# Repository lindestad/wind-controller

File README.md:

# LINDESTAD wind controller

Reproducible ESP32-C3 / Zephyr firmware and KiCad PCB for a four-fan simracing wind simulator.

[Hardware and manufacturing files](hardware/README.md) · [Schematic](hardware/reports/schematic.pdf) · [BOM](hardware/BOM.csv) · [Host integration](docs/host-integration.md)

The images are CAD renderings; representative USB/jack/eFuse models are visual aids.

Zephyr application for WindPCB B.3, ESP32-C3-WROOM-02-N4, four ARCTIC P14 Pro PST fans. Uses native USB Serial/JTAG, four 25 kHz hardware PWM outputs and four tach inputs. No external programmer is required for blank-flash recovery.

The assembled B.3 board is working. On 22 September 2026 it was programmed over native USB, tested with one and then two fans, and integrated with SimHub through Rig Companion. Live full-demand readings were approximately 2,470 and 2,410 RPM (fan rating 2,500 RPM); the user confirmed good airflow after correcting a reversed fan. This is functional bring-up evidence, not calibrated electrical or thermal qualification. See [validation scope](docs/validation.md).

## Repository layout

- `src/`, `include/`, `boards/`: firmware and custom Zephyr board definition.
- `hardware/`: native KiCad project, local libraries/models, BOM, Gerbers, CPL, STEP, PDFs, renders and exporter.
- `scripts/`, `tests/`: dependency setup, build, pin audit, stop-first flash and executable host tests.
- `integrations/simhub/`: source snapshot of the companion's SimHub bridge; no proprietary SDK DLLs.
- `reports/`: historical software/build/bring-up evidence, not a substitute for rerunning checks.

## Build

Windows workspace: `../wind-zephyr`, pinned to Zephyr **v4.4.2**. The required complete Zephyr SDK **1.0.1** is installed under `~/zephyr-sdk-1.0.1`. This project is a separate Git repository; SDK and dependency repositories are outside it.

Install Git, Python 3.12 (including `py`), CMake, Ninja and a host GCC (for the tests; Strawberry Perl's GCC works on Windows). Install the complete **Zephyr SDK 1.0.1** at `~/zephyr-sdk-1.0.1`, or pass its directory with `-Sdk`. Fetch the pinned source dependencies once:

```powershell
./scripts/setup.ps1
./scripts/build.ps1 -Pristine
../wind-zephyr/.venv/Scripts/python.exe tests/test_control.py
```

`build/zephyr/zephyr.bin` is the application build output. Use the Zephyr runner's generated flash configuration rather than guessing offsets. Build provenance and configuration checks are recorded in `reports/`. See `docs/validation.md` for scope and hardware acceptance items.

To recreate dependencies, create a Python 3.12 virtual environment in `../wind-zephyr/.venv`, install `west`, initialize the official Zephyr manifest at v4.4.2, run `west update`, install `zephyr/scripts/requirements.txt`, and run `west blobs fetch hal_espressif`. Use SDK 1.0.1. The frozen manifest is stored in `reports/west-frozen.yml`. No global Zephyr workspace was changed.

## USB and SimHub

Hold BOOT, press/release RESET, release BOOT. The ROM downloader should enumerate through USB-C even if application flash is blank. Connect a data-capable cable; barrel power is unnecessary for flashing. Run `west flash --esp-device COMx` from this workspace with the build directory specified, then press RESET if needed. The exact runner command is documented by `west flash -H -r esp32` and must match the installed esptool version. No eFuse/security programming or UART bridge is required.

For direct integration without Rig Companion, use SimHub **Custom Serial Devices**, sending ASCII `W,<left>,<right>\n` with integer demands 0–1000. The final character is one LF byte. Send every 100 ms or faster, including unchanged values. There is no Arduino/ShakeIt protocol emulation. USB returns the structured status frames below; Zephyr console/log noise remains disabled. Displaying warnings in SimHub needs a receiver/integration; transmission alone does not create a SimHub warning UI.

Zero and demands below 50 stop that side. A nonzero request first precharges for 750 ms, then attempts the commanded headers individually. Each gets a 250 ms full-speed kick; the next starts after at least 500 ms and three new filtered tach edges, or after a 2 s timeout if tach is absent. That timeout raises a per-header warning and advances the sequence, without stopping any output. Losing tach for 2 s after startup also warns while maintaining the requested duty. One to four fans may occupy any headers; no fan-count setting is required. Even zero fans produces warnings rather than a shutdown. Missing headers can delay later fans by 2 s each (up to 6.75 s from command to the fourth header's kick).

An empty header, stalled motor and broken tach wire cannot be distinguished electrically. Warnings mean **no tach while commanded**, not a confirmed missing fan. There are no repeated automatic startup kicks. Three new edges clear a warning; stopping that side clears its warning and the next start checks again. Do not hot-plug fans; switch off supplies before moving connectors.

Every 500 ms, USB transmits `S,1,<mode>,<mask>\n` (8 ASCII bytes). Version is 1; mode is `0` off, `1` precharging, `2` active (including warnings), `3` command timeout, or `4` fault. Mask is one uppercase hexadecimal digit: bits `1/2/4/8` correspond to L1/L2/R1/R2 without tach. For example `S,1,2,A\n` means active, with L2 and R2 warnings. Warnings are live and only apply after a startup attempt, so a clear mask at boot does not prove a fan is connected. STATUS stays lit when fan power is enabled. The red FAULT LED remains controlled by the hardware eFuse, not these firmware warnings.

Status transmission uses a bounded interrupt-driven buffer; a host that stops reading cannot block the control loop or command timeout. Pending reports can be stale after a host pause; a receiver must wait for fresh periodic reports before relying on them. Reports describe requested controller state, not measured fan-supply voltage or verified motor motion.

Only valid complete demand frames refresh the 500 ms command deadline. Overlong, malformed and partial frames are rejected. RX-budget saturation and output failures still stop operation and require reset; warnings do not bypass these protections. Commanded stop sets all PWM inputs low before removing fan power. Abrupt USB loss/reset can still cause the documented brief capacitor-powered twitch/coasting.

## Extended telemetry

Extended telemetry is also sent about once per second: `T,2,<mode>,<warning_hex>,<uptime_ms>,<accepted>,<rejected>,<rpm_L1>,<rpm_L2>,<rpm_R1>,<rpm_R2>,<pwm_L1>,<pwm_L2>,<pwm_R1>,<pwm_R2>\n`. RPM uses edge-count differences over the actual sample interval and assumes two pulses per revolution; absolute accuracy needs independent measurement. PWM values are per-header 0–1000 output demands including startup kicks. No supply voltage/current/temperature measurement exists. The existing S1 reports remain unchanged; consumers should ignore recognized additional report types. Rig Companion now owns USB and receives SimHub vehicle speed through its localhost bridge; see [host integration](docs/host-integration.md).

## Routine firmware updates

After building, use Rig Companion’s **Release USB for firmware update** button (or close any direct serial owner) and run `./scripts/flash.ps1 -Port COM4` (substitute the current port). The helper sends stop commands, requires repeated OFF reports for two seconds, then invokes the generated Zephyr flash runner. It aborts if it cannot confirm OFF. Firmware starts with fan power disabled and needs a new valid demand before running. Never resume the command sender during flashing.

The board's external enable pull-down is intended to keep incoming fan power off in ROM download/reset. This makes leaving 12 V connected a supported design intent for routine updates with the stop-first helper, **not a measured guarantee of no movement**: the MCU cannot measure output capacitor voltage, and reset can release PWM before stored energy drains. Disconnect 12 V whenever zero fan movement matters, or for blank/corrupt firmware recovery. The helper cannot work on older firmware without status reports. Hold BOOT/RESET and use the ordinary Zephyr runner with 12 V disconnected in that case.

The watchdog requests a whole-system reset. The ESP32 driver uses an interrupt stage followed by a reset stage; a configured 500 ms stage interval is approximately 1 s to hardware reset, not a 500 ms reset guarantee. The ordinary command timeout runs separately. No hardware runtime timing guarantee is claimed before measurement.

## Pin map

| Function | GPIO |
|---|---|
| L1/L2/R1/R2 PWM sink gates | 4 / 5 / 6 / 7 |
| L1/L2/R1/R2 tach | 0 / 1 / 3 / 20 |
| Fan power enable | 10 |
| Status LED | 21 |
| Native USB D− / D+ | 18 / 19 |
| BOOT | 9 |
| Reserved boot straps | 2 / 8 |

The DTS uses the WROOM N4 module definition, not a development board with UART0 on GPIO20/21. UART0/1, radios, logging and power management are disabled. The eFuse FLT signal is not wired to the MCU, so firmware cannot classify its faults or measure supply voltage/current.

The LEDC child `inverted` property initializes the stopped output high. Runtime requests use normal polarity and `(1000 − fan_demand) × 40 ns` gate pulse width; the transistor provides the physical inversion. The pinned driver's implementation was checked to distinguish initial idle level from runtime polarity flags.

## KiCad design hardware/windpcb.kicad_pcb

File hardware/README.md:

# WindPCB B.3 — editable hardware and manufacturing release

70 × 64 mm, black solder mask, white silkscreen, two-layer 1.6 mm FR-4 / 1 oz copper.
ESP32-C3-WROOM-02-N4; four ARCTIC P14 Pro PST headers; native USB-C; protected 12 V input.

These are CAD renders, not photographs. J1, J2 and U4 have representative visual bodies;
their manufacturer drawings and electrical pads govern assembly.

## Reproduce the board

1. Install **KiCad 10.0**, including its standard symbol, footprint and 3D libraries.
2. Open `windpcb.kicad_pro`. All project-specific symbols, footprints and visual models
   are under `libraries/`; library tables use `${KIPRJMOD}`. Standard STEP models use
   `${KICAD10_3DMODEL_DIR}`. No files from the author's KiCad folder are needed.
3. Use [BOM.csv](BOM.csv), [schematic PDF](reports/schematic.pdf) and
   [assembly drawing](reports/assembly-top.pdf) to inspect the release.
4. Fabrication input: [Gerber ZIP](manufacturing/windpcb-revb-gerbers.zip), including
   copper, masks, silkscreens, outline, separate PTH/NPTH drilling and front paste.
5. Full assembly inputs: [PCBA BOM](manufacturing/assembly/PCBA-BOM.csv) and
   [PCBA CPL](manufacturing/assembly/PCBA-CPL.csv): **70 placements, 33 MPNs,
   63 SMT + 7 through-hole**. Do not use the SMT-only files for full assembly.
6. Select black mask / white silk, lead-free HASL, top-side assembly, and customer-added
   tooling holes. Retain individual placement review. Firmware is flashed afterward.

J1 takes a **5.5 × 2.5 mm centre-positive 12 V** barrel plug. Use a regulated supply
with sufficient startup margin (at least 3 A recommended). Each fan has its own header;
leave PST daisy-chain sockets unused. Pin order: **1 GND, 2 +12 V, 3 tach, 4 PWM**.

## Placement and process review

The included CPL is the original submitted file, with explicit connector/capacitor
insertion-origin offsets. **JLC subsequently corrected several component orientations
in its own assembly system. The final numeric machine placement file was not supplied.**
This release therefore requires a fresh supplier placement review; uploading the CPL
alone does not reproduce that approval. Verify every polarized part/pin 1 against the
native CAD and assembly drawing, especially Q1–Q9, U2/U3/U4, J2–J6, D1–D4 and C6/C9.
The first assembled board has since operated successfully with the firmware.

U4 TPS25970LRPWR has ten electrical terminals, even when a supplier's generic visual
model shows sixteen leads. Its 16 split paste apertures are intentional. Preserve the
TI-derived RPW0010A lands and 0.100 mm stencil prescription; ask the assembler to review
the eFuse, USB-C, and ESP32 thermal-via soldering process for its selected finish.

H1–H4: 3.2 mm M3 mounting holes, 63 × 57 mm spacing. H5/H6 are 1.152 mm NPTH tooling
holes with 0.148 mm mask expansion. Their centres are (10, 3.5) and (60, 60.5) mm from
the upper-left corner. The CPL origin is the lower-left corner; X right, Y up.

## Regenerate and verify

Run the exporter with KiCad's Python (which provides `pcbnew`). On Windows:

```powershell
& 'C:/Program Files/KiCad/10.0/bin/python.exe' -m pip install --target hardware/tools/vendor -r hardware/tools/requirements.txt
& 'C:/Program Files/KiCad/10.0/bin/python.exe' hardware/tools/export.py
```

On another installation, put `kicad-cli` on PATH or set `KICAD_CLI` and use a Python
environment that can import KiCad 10's `pcbnew`. The exporter runs ERC, full DRC with
schematic parity, checks every pad/net, exports manufacturing files/BOM/CPL, PDFs,
board-only STEP, pictures and SHA256 hashes. It does **not** rebuild or reroute the PCB.
Historical one-time layout generators were deliberately not included as build steps.

Engineering specifications and revision notes are in `docs/`. Their pre-order wording
and references to historical local reports describe earlier reviews, not the current
hardware test status. The root README and `docs/validation.md` describe current tests.
Private supplier order/account records are not part of this public release.

Sources: [TI TPS2597](https://www.ti.com/lit/ds/symlink/tps2597.pdf),
[ARCTIC P14 Pro PST](https://support.arctic.de/p14-pro-pst),
[JLC tooling guide](https://jlcpcb.com/help/article/how-to-add-tooling-holes-for-pcb-assembly-order).

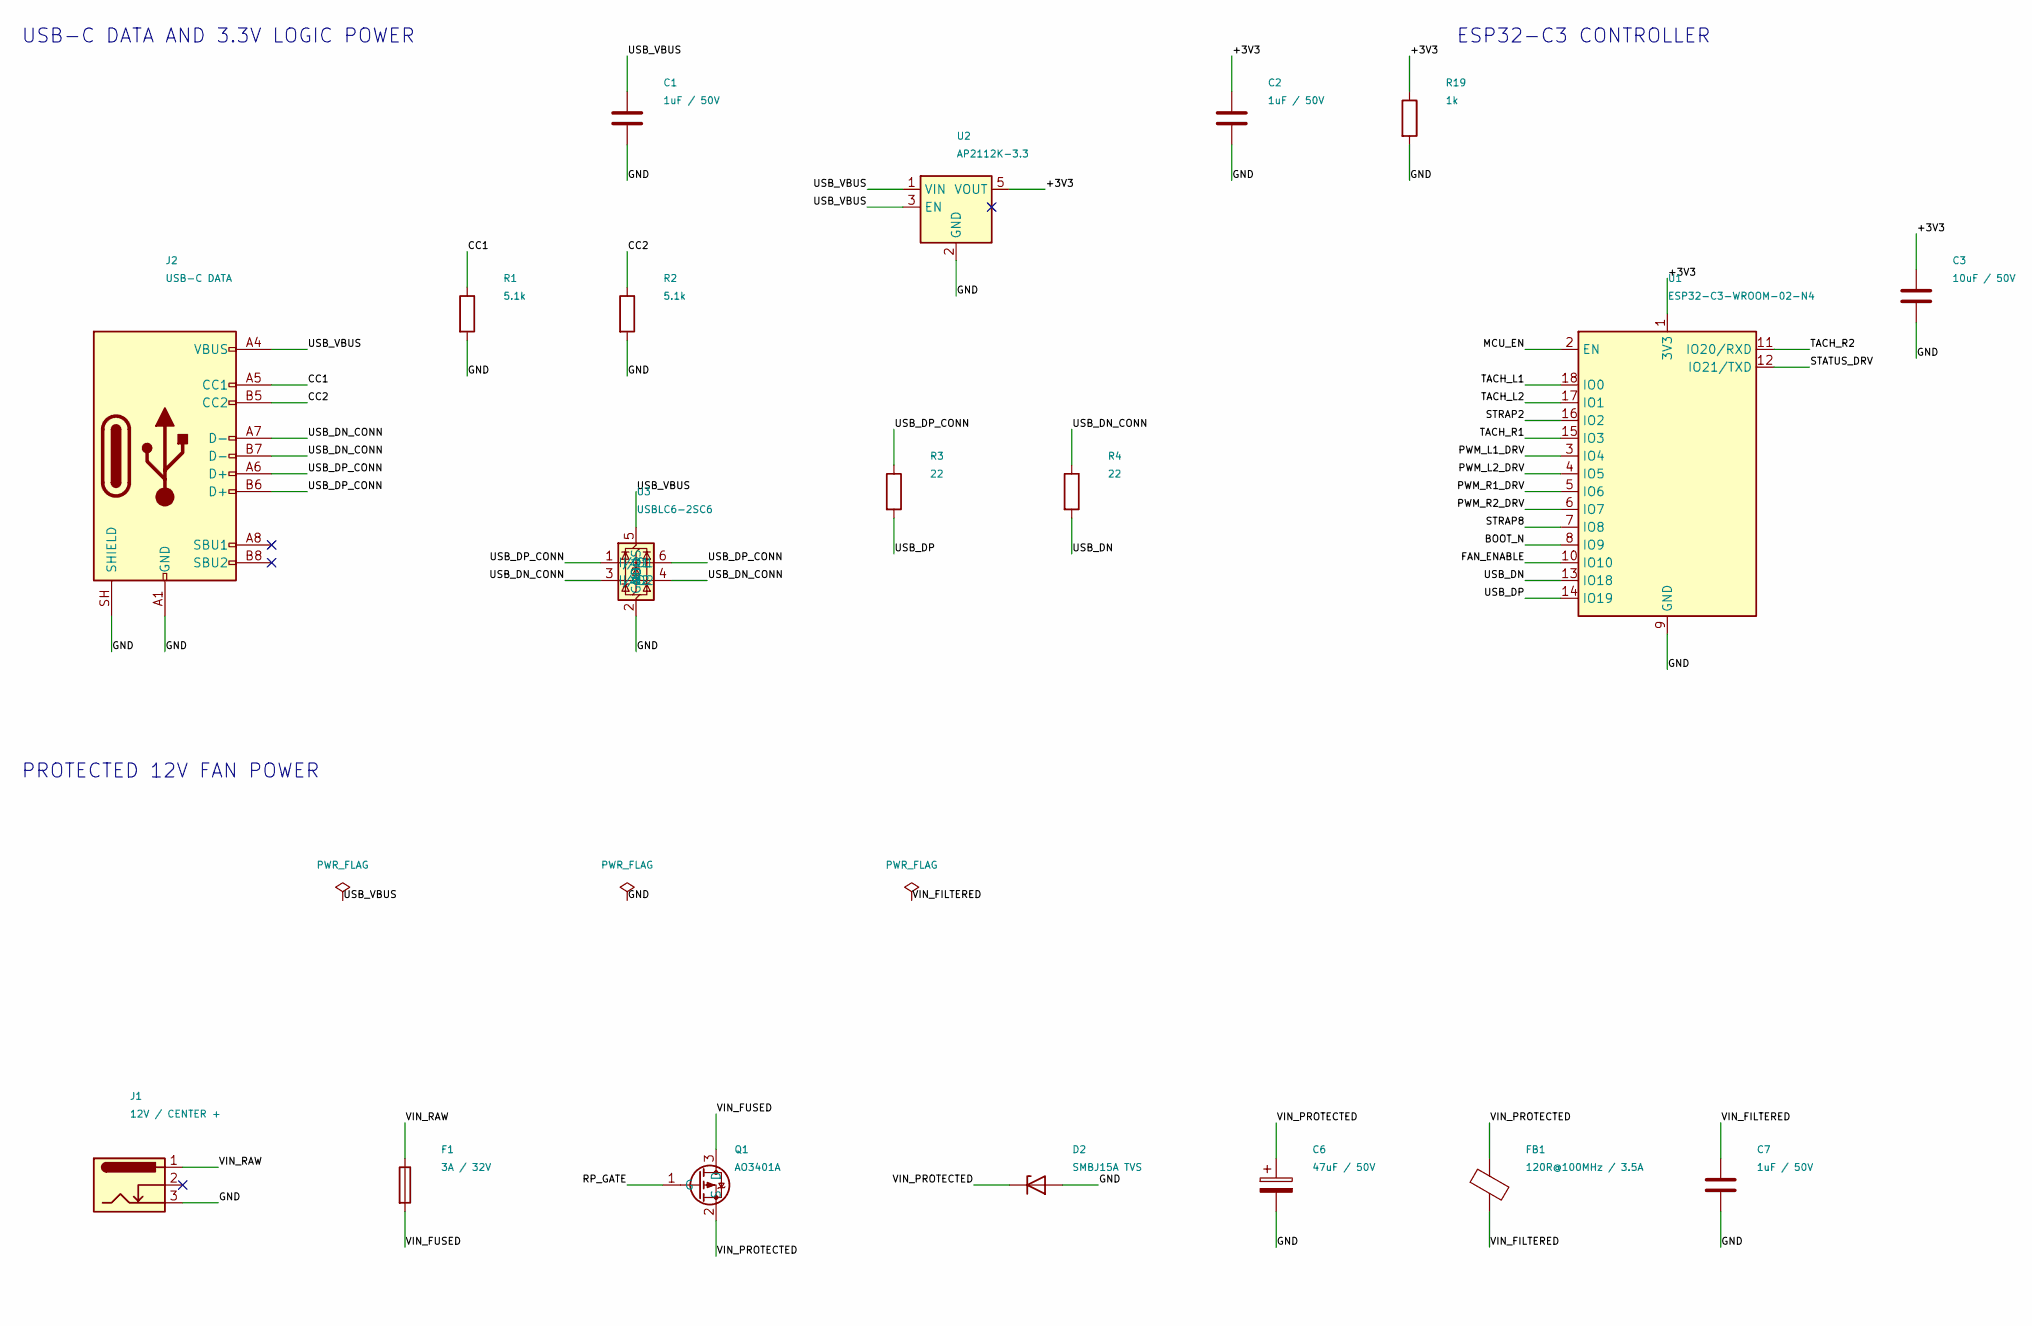
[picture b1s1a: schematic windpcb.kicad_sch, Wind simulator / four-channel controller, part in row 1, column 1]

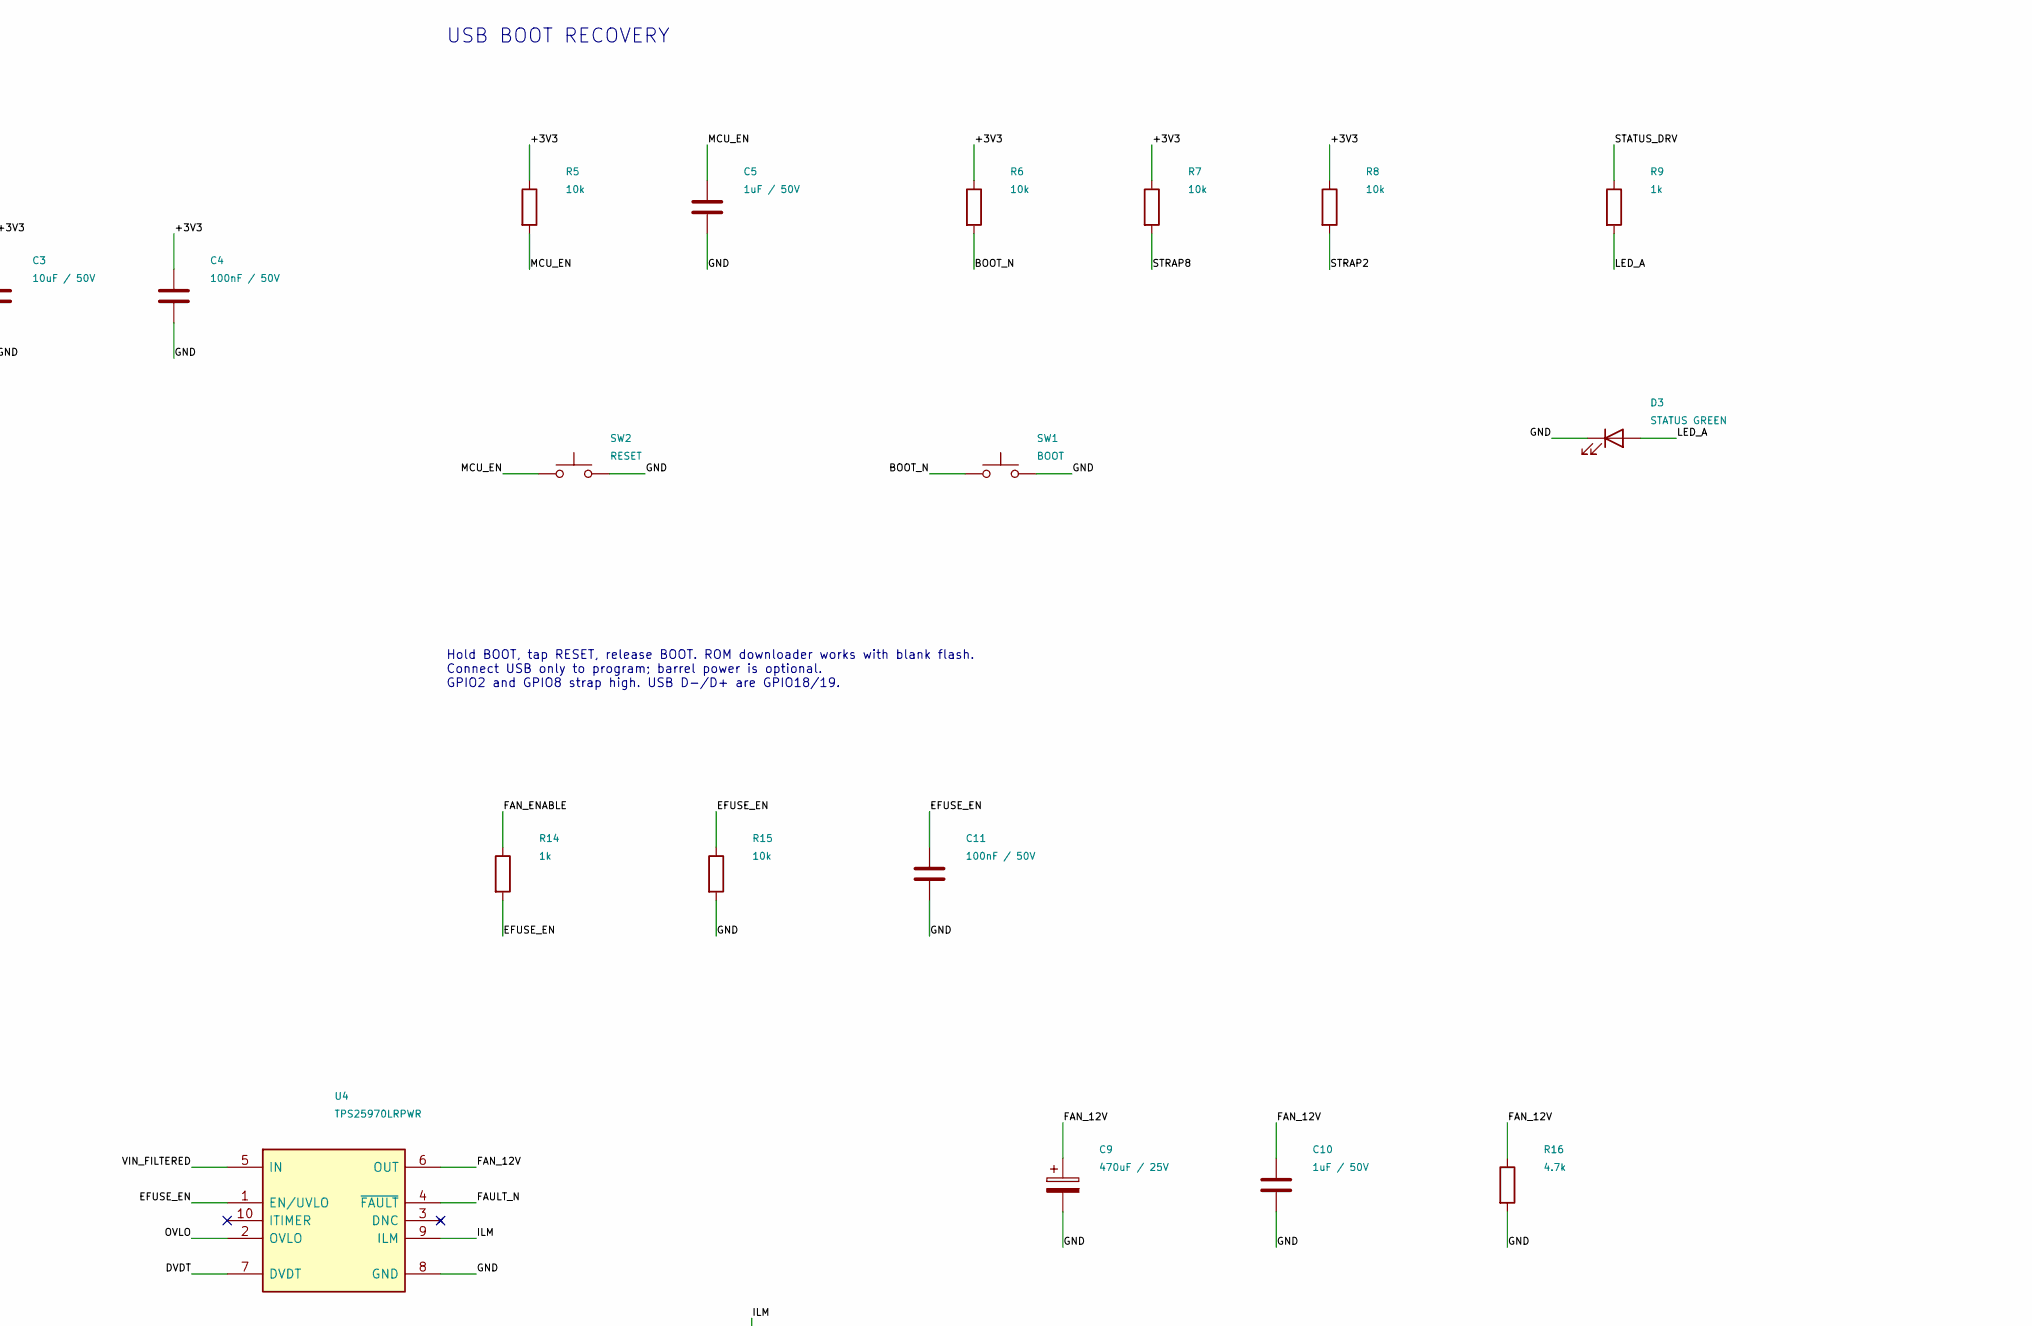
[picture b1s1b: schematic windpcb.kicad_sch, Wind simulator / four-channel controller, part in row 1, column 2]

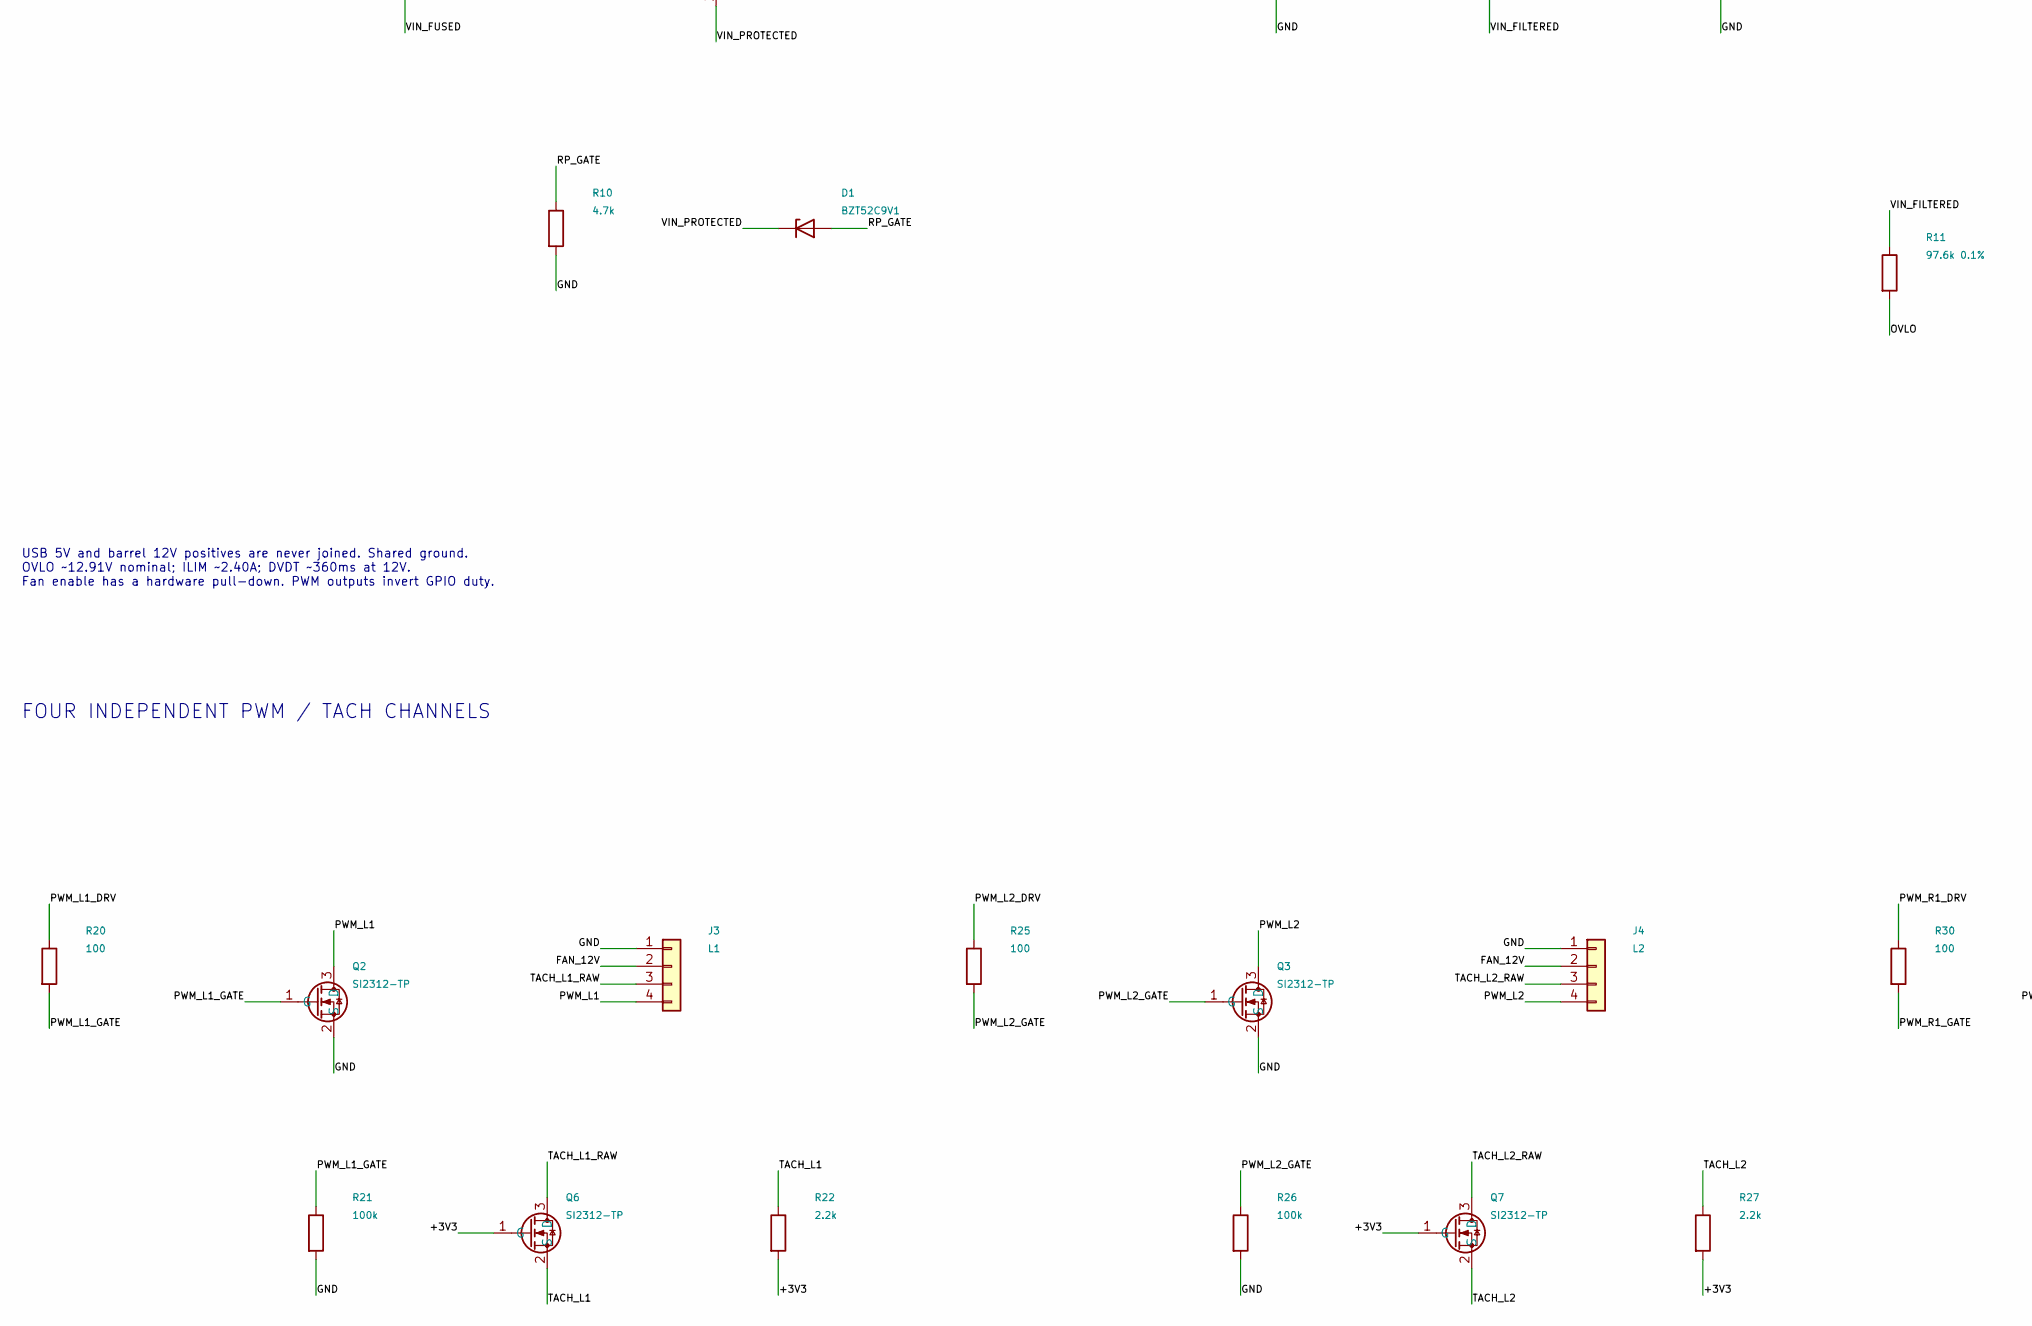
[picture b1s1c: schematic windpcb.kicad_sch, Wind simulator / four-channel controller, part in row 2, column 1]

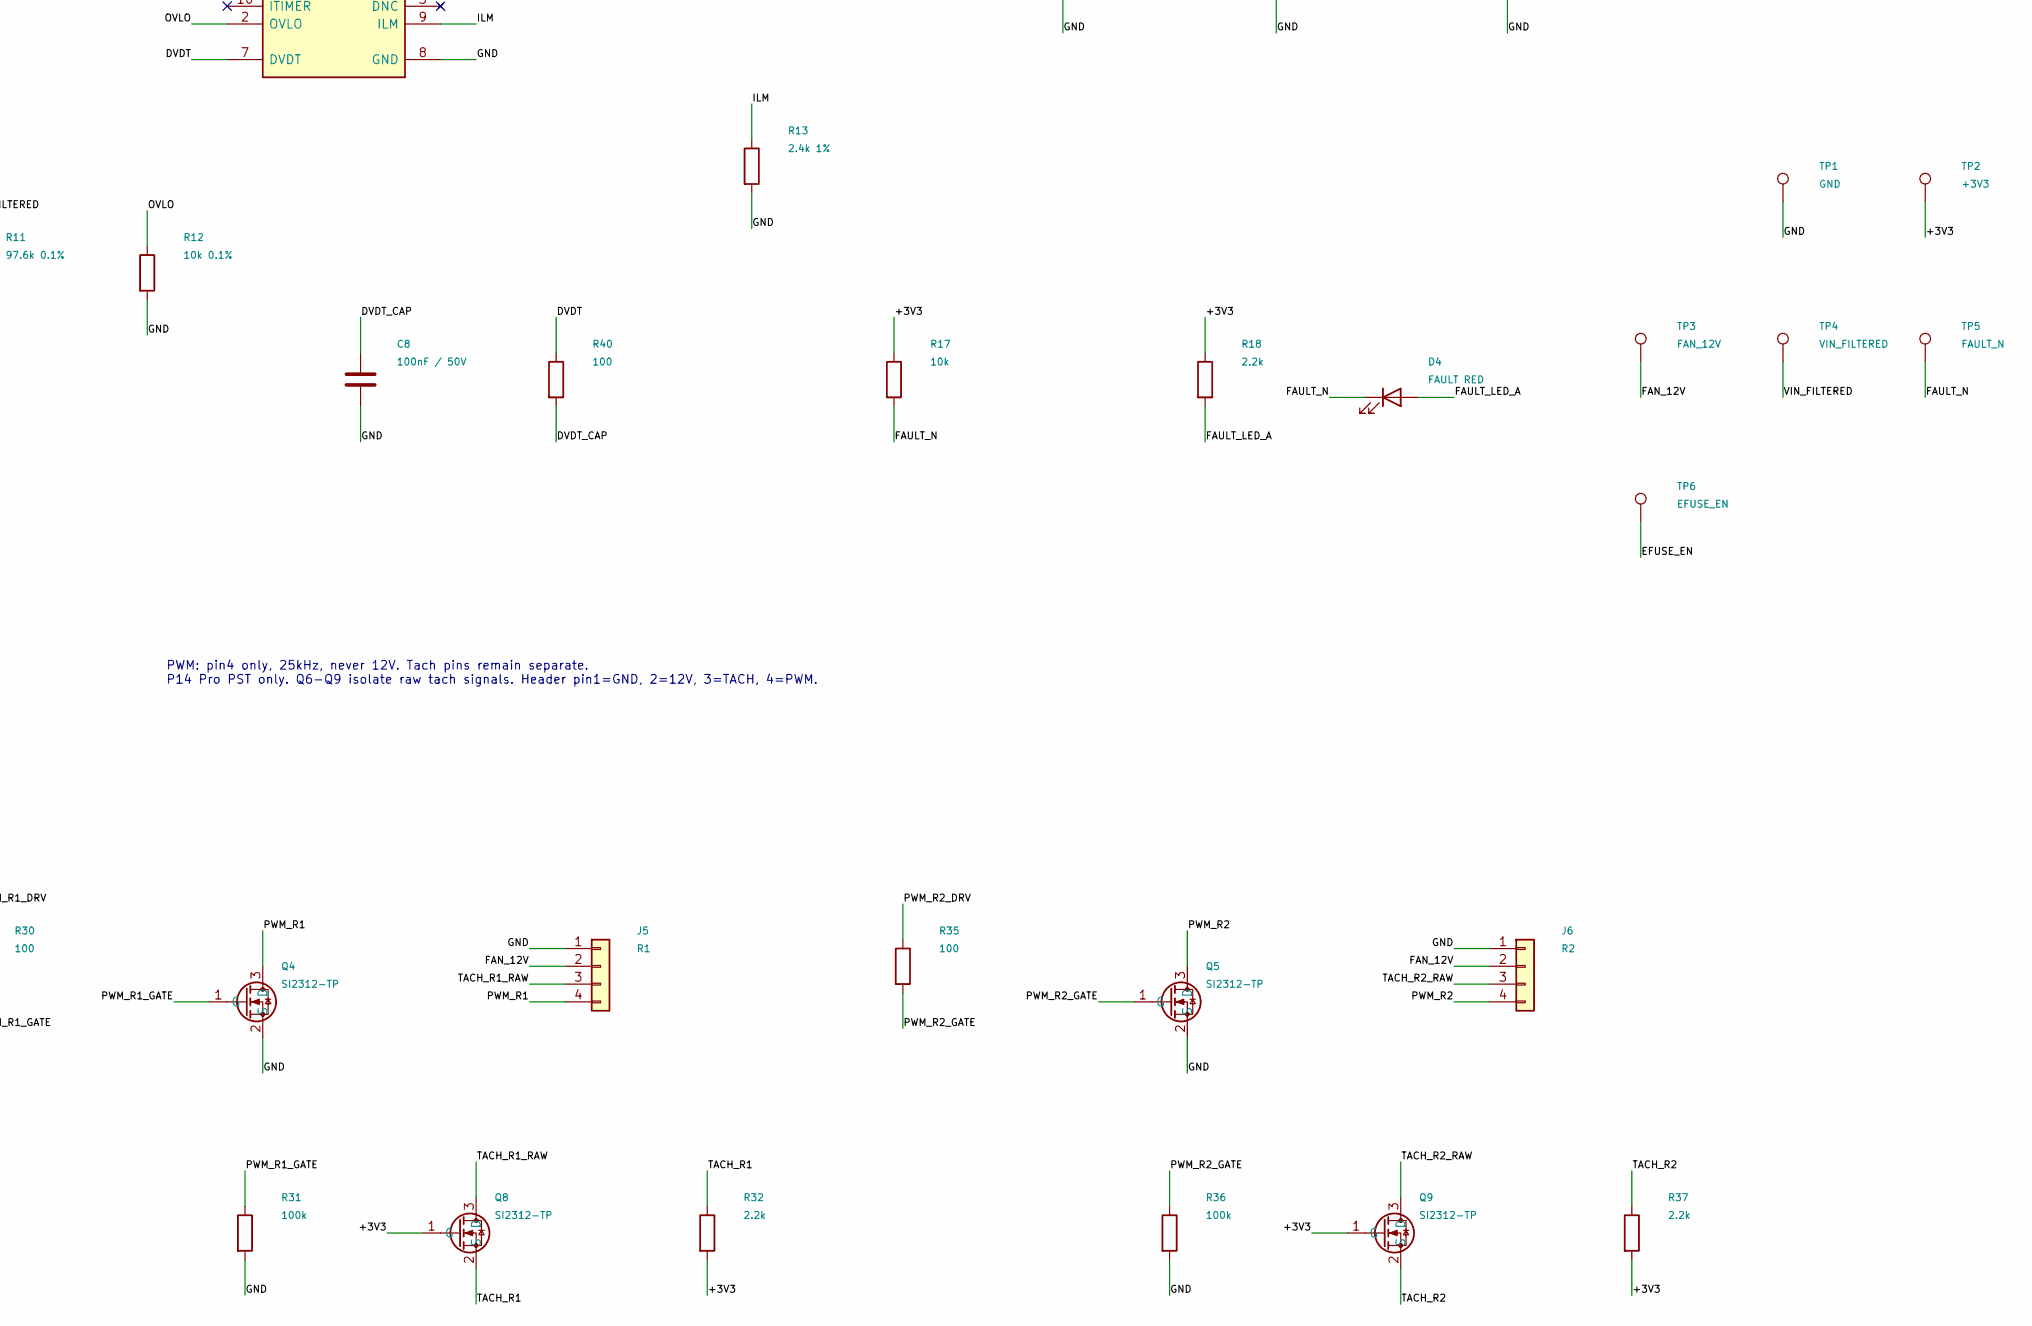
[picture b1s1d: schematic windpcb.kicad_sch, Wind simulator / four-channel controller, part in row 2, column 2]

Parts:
C1, C2, C5: 1uF / 50V; Capacitor_SMD_C_0603_1608Metric; MPN CL10A105KB8NNNC; LCSC C15849
C3: 10uF / 50V; Capacitor_SMD_C_0805_2012Metric; MPN GRM21BR61H106KE43L; LCSC C440198
C4, C8, C11: 100nF / 50V; Capacitor_SMD_C_0603_1608Metric; MPN CC0603KRX7R9BB104; LCSC C14663
C6: 47uF / 50V; Capacitor_THT_CP_Radial_D6.3mm_P2.50mm; MPN EEUFR1H470; LCSC C407950
C7, C10: 1uF / 50V; Capacitor_SMD_C_0805_2012Metric; MPN CL21B105KBFNNNE; LCSC C28323
C9: 470uF / 25V; Capacitor_THT_CP_Radial_D10.0mm_P5.00mm; MPN EEUFR1E471; LCSC C407944
D1: BZT52C9V1; Diode_SMD_D_SOD-123; MPN BZT52C9V1-7-F; LCSC C260913
D2: SMBJ15A TVS; Diode_SMD_D_SMB; MPN SMBJ15A; LCSC C83846
D3: STATUS GREEN; LED_SMD_LED_0805_2012Metric; MPN KT-0805G; LCSC C2297
D4: FAULT RED; LED_SMD_LED_0603_1608Metric; MPN KT-0603R; LCSC C2286
F1: 3A / 32V; Fuse_Fuse_1206_3216Metric; MPN 0466003.NRHF; LCSC C14165
FB1: 120R@100MHz / 3.5A; Inductor_SMD_L_1206_3216Metric; MPN BLM31PG121SN1L; LCSC C85841
J1: 12V / CENTER +; BarrelJack_XKB_DC-005-5A-2.5; MPN DC-005-5A-2.5; LCSC C381115
J2: USB-C DATA; Connector_USB_USB_C_Receptacle_HRO_TYPE-C-31-M-12; MPN TYPE-C-31-M-12; LCSC C165948
J3: L1; Connector_FanPinHeader_1x04_P2.54mm_Vertical; MPN 470531000; LCSC C240840
J4: L2; Connector_FanPinHeader_1x04_P2.54mm_Vertical; MPN 470531000; LCSC C240840
J5: R1; Connector_FanPinHeader_1x04_P2.54mm_Vertical; MPN 470531000; LCSC C240840
J6: R2; Connector_FanPinHeader_1x04_P2.54mm_Vertical; MPN 470531000; LCSC C240840
Q1: AO3401A; Package_TO_SOT_SMD_SOT-23; MPN AO3401A; LCSC C15127
Q2, Q3, Q4, Q5, Q6, Q7, Q8, Q9: SI2312-TP; Package_TO_SOT_SMD_SOT-23; MPN SI2312-TP; LCSC C6488168
R1, R2: 5.1k; Resistor_SMD_R_0603_1608Metric; MPN 0603WAF5101T5E; LCSC C23186
R3, R4: 22; Resistor_SMD_R_0603_1608Metric; MPN 0603WAF220JT5E; LCSC C23345
R5, R6, R7, R8, R15, R17: 10k; Resistor_SMD_R_0603_1608Metric; MPN 0603WAF1002T5E; LCSC C25804
R9, R14, R19: 1k; Resistor_SMD_R_0603_1608Metric; MPN 0603WAF1001T5E; LCSC C21190
R10, R16: 4.7k; Resistor_SMD_R_0603_1608Metric; MPN 0603WAF4701T5E; LCSC C23162
R11: 97.6k 0.1%; Resistor_SMD_R_0603_1608Metric; MPN RT0603BRE0797K6L; LCSC C862326
R12: 10k 0.1%; Resistor_SMD_R_0603_1608Metric; MPN RT0603BRD0710KL; LCSC C95204
R13: 2.4k 1%; Resistor_SMD_R_0603_1608Metric; MPN 0603WAF2401T5E; LCSC C22940
R18, R22, R27, R32, R37: 2.2k; Resistor_SMD_R_0603_1608Metric; MPN 0603WAF2201T5E; LCSC C4190
R20, R25, R30, R35, R40: 100; Resistor_SMD_R_0603_1608Metric; MPN 0603WAF1000T5E; LCSC C22775
R21, R26, R31, R36: 100k; Resistor_SMD_R_0603_1608Metric; MPN 0603WAF1003T5E; LCSC C25803
SW1: BOOT; Button_Switch_SMD_SW_SPST_TL3342; MPN TL3342F160QG; LCSC C2886898
SW2: RESET; Button_Switch_SMD_SW_SPST_TL3342; MPN TL3342F160QG; LCSC C2886898
TP1: GND; TestPoint_TestPoint_Pad_D1.5mm; MPN PCB test point
TP2: +3V3; TestPoint_TestPoint_Pad_D1.5mm; MPN PCB test point
TP3: FAN_12V; TestPoint_TestPoint_Pad_D1.5mm; MPN PCB test point
TP4: VIN_FILTERED; TestPoint_TestPoint_Pad_D1.5mm; MPN PCB test point
TP5: FAULT_N; TestPoint_TestPoint_Pad_D1.5mm; MPN PCB test point
TP6: EFUSE_EN; TestPoint_TestPoint_Pad_D1.5mm; MPN PCB test point
U1: ESP32-C3-WROOM-02-N4; RF_Module_ESP32-C3-WROOM-02; MPN ESP32-C3-WROOM-02-N4; LCSC C2934560
U2: AP2112K-3.3; Package_TO_SOT_SMD_SOT-23-5; MPN AP2112K-3.3TRG1; LCSC C51118
U3: USBLC6-2SC6; Package_TO_SOT_SMD_SOT-23-6; MPN USBLC6-2SC6; LCSC C7519
U4: TPS25970LRPWR; TPS25970_RPW0010A_2x2mm; MPN TPS25970LRPWR; LCSC C3662801

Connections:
/+3V3: C2.1, C3.1, C4.1, Q6.1 (G), Q7.1 (G), Q8.1 (G), Q9.1 (G), R5.1, R6.1, R7.1, R8.1, R17.1, R18.1, R19.1, R22.2, R27.2, R32.2, R37.2, TP2.1, U1.1 (3V3), U2.5 (VOUT)
/BOOT_N: R6.2, SW1.1, U1.8 (IO9)
/CC1: J2.A5 (CC1), R1.1
/CC2: J2.B5 (CC2), R2.1
/DVDT: R40.1, U4.7 (DVDT)
/DVDT_CAP: C8.1, R40.2
/EFUSE_EN: C11.1, R14.2, R15.1, TP6.1, U4.1 (EN/UVLO)
/FAN_12V: C9.1, C10.1, J3.2, J4.2, J5.2, J6.2, R16.1, TP3.1, U4.6 (OUT)
/FAN_ENABLE: R14.1, U1.10 (IO10)
/FAULT_LED_A: D4.2 (A), R18.2
/FAULT_N: D4.1 (K), R17.2, TP5.1, U4.4 (~FAULT)
/GND: C1.2, C2.2, C3.2, C4.2, C5.2, C6.2, C7.2, C8.2, C9.2, C10.2, C11.2, D2.2 (A), D3.1 (K), J1.3, J2.A1 (GND), J2.A12 (GND), J2.B1 (GND), J2.B12 (GND), J2.SH (SHIELD), J3.1, J4.1, J5.1, J6.1, Q2.2 (S), Q3.2 (S), Q4.2 (S), Q5.2 (S), R1.2, R2.2, R10.2, R12.2, R13.2, R15.2, R16.2, R19.2, R21.2, R26.2, R31.2, R36.2, SW1.2, SW2.2, TP1.1, U1.9 (GND), U1.19 (GND), U2.2 (GND), U3.2 (GND), U4.8 (GND)
/ILM: R13.1, U4.9 (ILM)
/LED_A: D3.2 (A), R9.2
/MCU_EN: C5.1, R5.2, SW2.1, U1.2 (EN)
/OVLO: R11.2, R12.1, U4.2 (OVLO)
/PWM_L1: J3.4, Q2.3 (D)
/PWM_L1_DRV: R20.1, U1.3 (IO4)
/PWM_L1_GATE: Q2.1 (G), R20.2, R21.1
/PWM_L2: J4.4, Q3.3 (D)
/PWM_L2_DRV: R25.1, U1.4 (IO5)
/PWM_L2_GATE: Q3.1 (G), R25.2, R26.1
/PWM_R1: J5.4, Q4.3 (D)
/PWM_R1_DRV: R30.1, U1.5 (IO6)
/PWM_R1_GATE: Q4.1 (G), R30.2, R31.1
/PWM_R2: J6.4, Q5.3 (D)
/PWM_R2_DRV: R35.1, U1.6 (IO7)
/PWM_R2_GATE: Q5.1 (G), R35.2, R36.1
/RP_GATE: D1.2 (A), Q1.1 (G), R10.1
/STATUS_DRV: R9.1, U1.12 (IO21/TXD)
/STRAP2: R8.2, U1.16 (IO2)
/STRAP8: R7.2, U1.7 (IO8)
/TACH_L1: Q6.2 (S), R22.1, U1.18 (IO0)
/TACH_L1_RAW: J3.3, Q6.3 (D)
/TACH_L2: Q7.2 (S), R27.1, U1.17 (IO1)
/TACH_L2_RAW: J4.3, Q7.3 (D)
/TACH_R1: Q8.2 (S), R32.1, U1.15 (IO3)
/TACH_R1_RAW: J5.3, Q8.3 (D)
/TACH_R2: Q9.2 (S), R37.1, U1.11 (IO20/RXD)
/TACH_R2_RAW: J6.3, Q9.3 (D)
/USB_DN: R4.2, U1.13 (IO18)
/USB_DN_CONN: J2.A7 (D-), J2.B7 (D-), R4.1, U3.3 (I/O2), U3.4 (I/O2)
/USB_DP: R3.2, U1.14 (IO19)
/USB_DP_CONN: J2.A6 (D+), J2.B6 (D+), R3.1, U3.1 (I/O1), U3.6 (I/O1)
/USB_VBUS: C1.1, J2.A4 (VBUS), J2.A9 (VBUS), J2.B4 (VBUS), J2.B9 (VBUS), U2.1 (VIN), U2.3 (EN), U3.5 (VBUS)
/VIN_FILTERED: C7.1, FB1.2, R11.1, TP4.1, U4.5 (IN)
/VIN_FUSED: F1.2, Q1.3 (D)
/VIN_PROTECTED: C6.1, D1.1 (K), D2.1 (K), FB1.1, Q1.2 (S)
/VIN_RAW: F1.1, J1.1

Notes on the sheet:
USB-C DATA AND 3.3V LOGIC POWER
ESP32-C3 CONTROLLER
USB BOOT RECOVERY
PROTECTED 12V FAN POWER
FOUR INDEPENDENT PWM / TACH CHANNELS
Hold BOOT, tap RESET, release BOOT. ROM downloader works with blank flash. Connect USB only to program; barrel power is optional. GPIO2 and GPIO8 strap high. USB D-/D+ are GPIO18/19.
USB 5V and barrel 12V positives are never joined. Shared ground. OVLO ~12.91V nominal; ILIM ~2.40A; DVDT ~360ms at 12V. Fan enable has a hardware pull-down. PWM outputs invert GPIO duty.
PWM: pin4 only, 25kHz, never 12V. Tach pins remain separate. P14 Pro PST only. Q6-Q9 isolate raw tach signals. Header pin1=GND, 2=12V, 3=TACH, 4=PWM.
